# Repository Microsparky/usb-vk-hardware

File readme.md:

# USB Volume Knob

<!--> TODO Readme

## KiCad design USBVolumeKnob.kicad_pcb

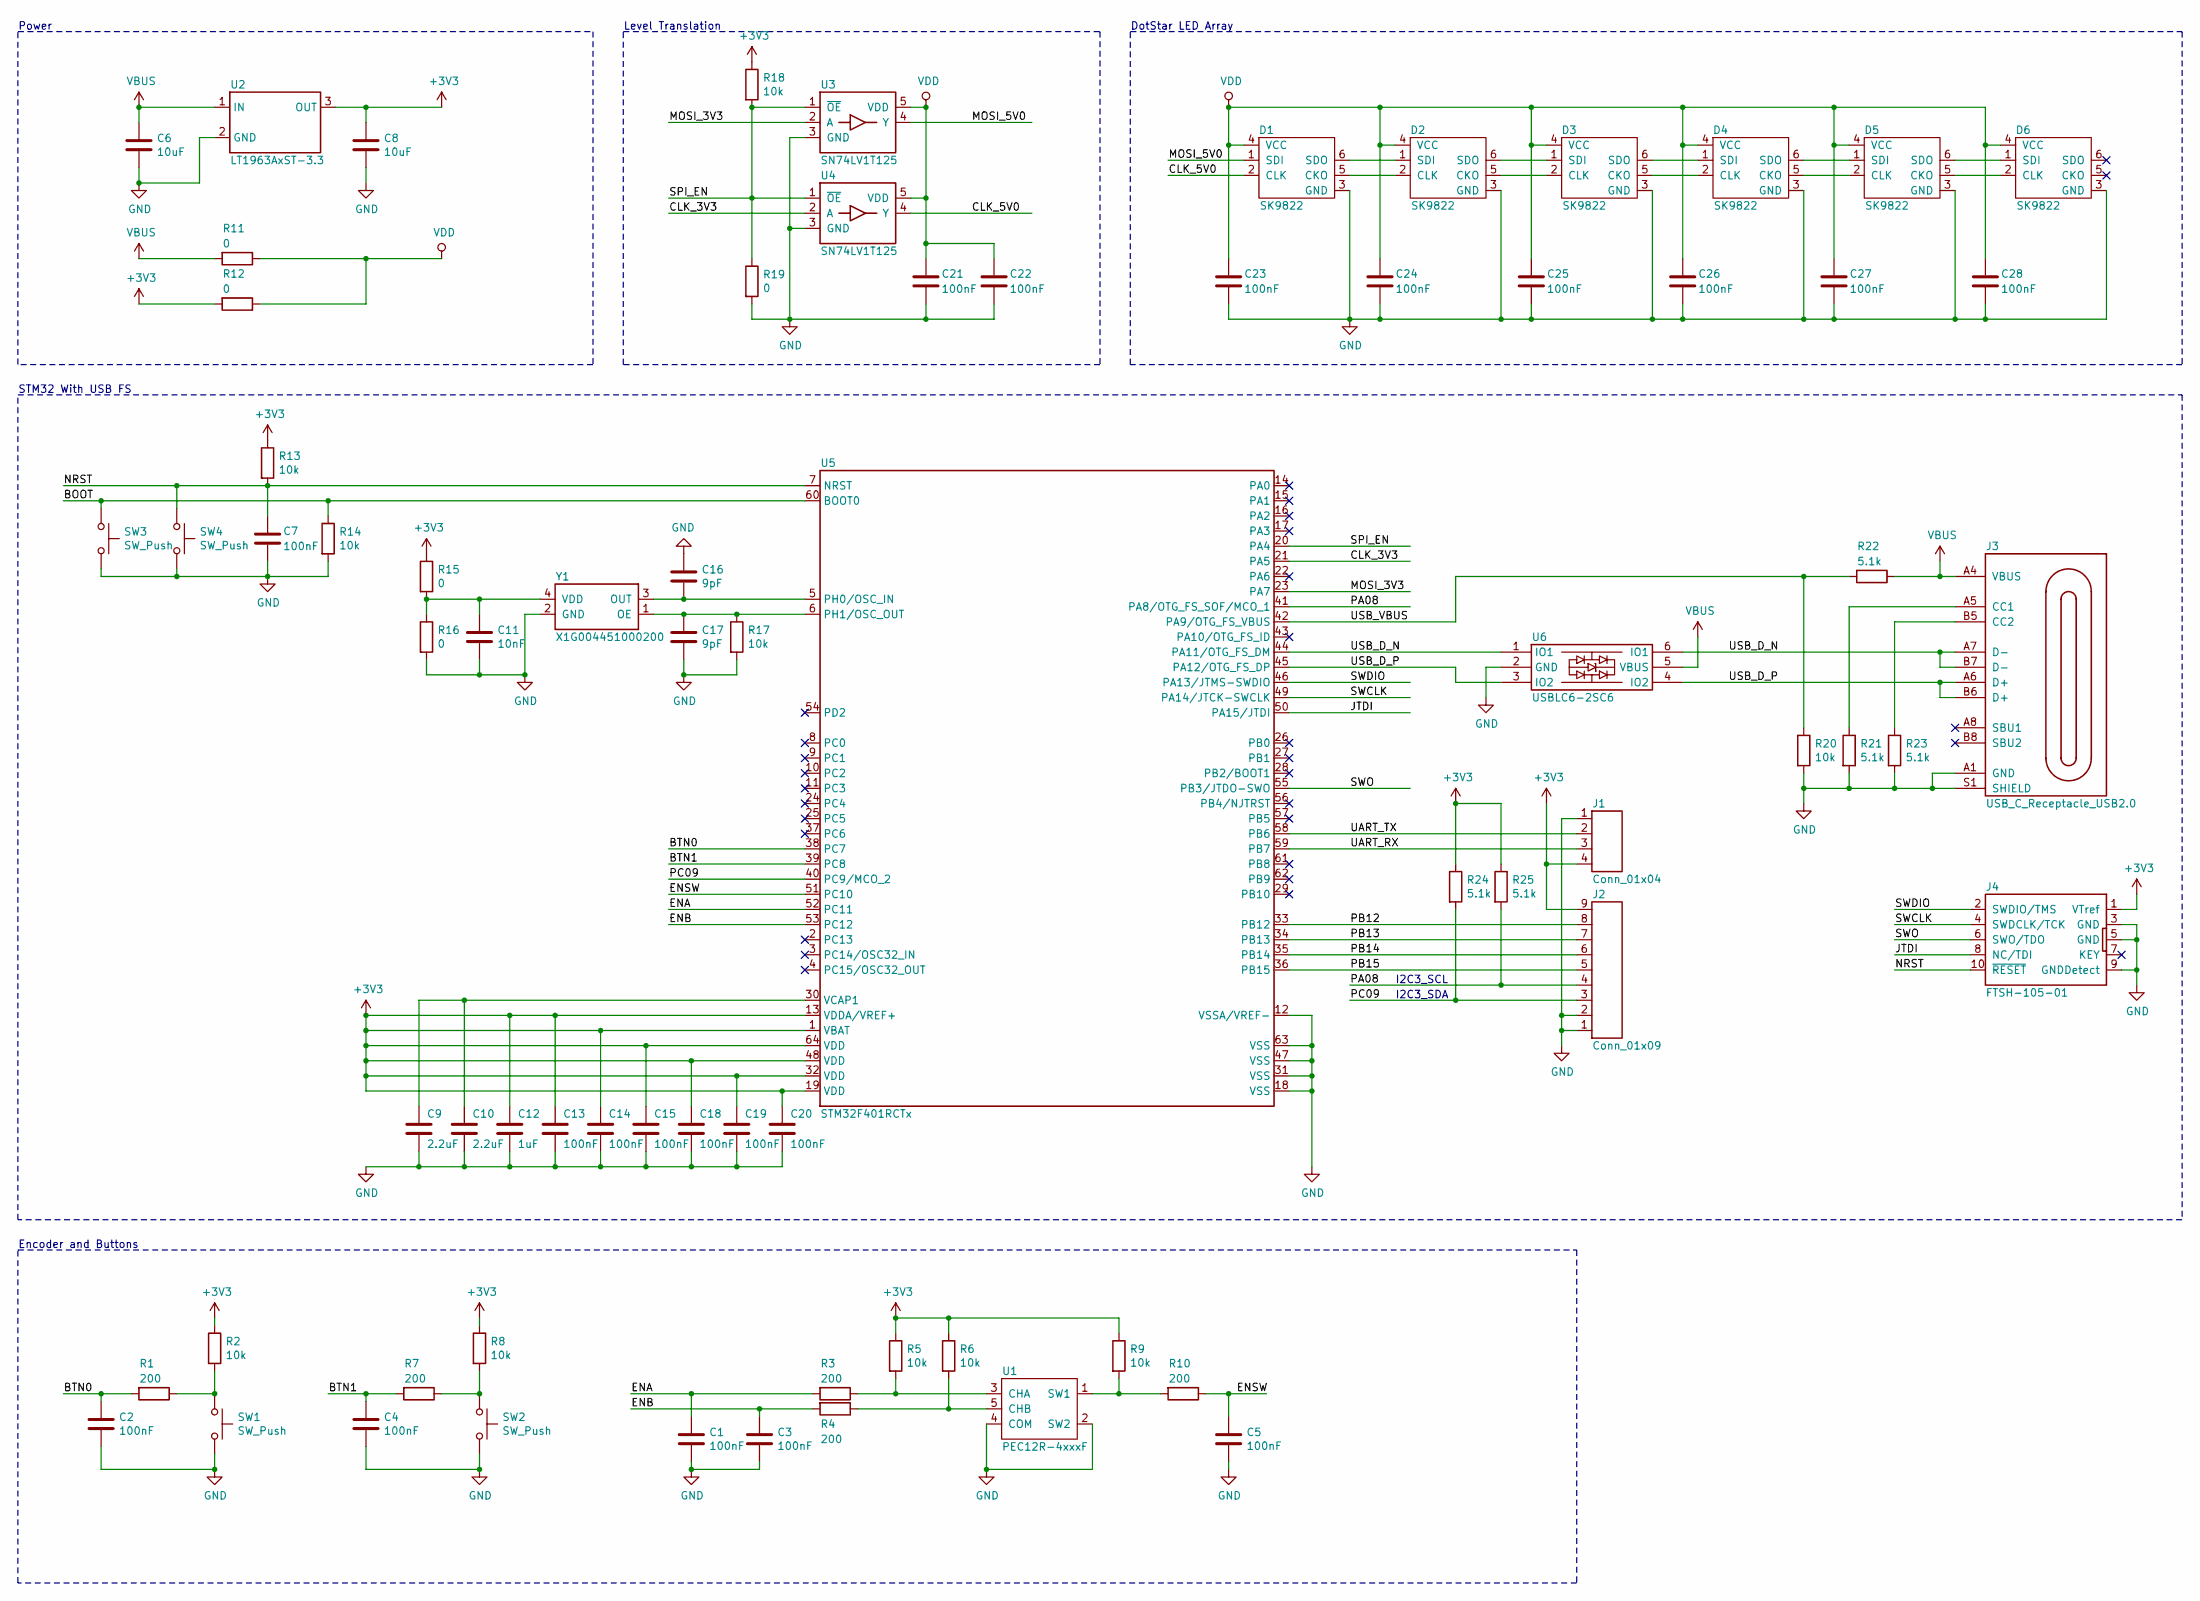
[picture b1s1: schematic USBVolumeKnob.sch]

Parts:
C1, C2, C3, C4, C5, C7, C13, C14, C15, C18, C19, C20, C21, C22, C23, C24, C25, C26, C27, C28: 100nF; C_0603_1608Metric_Pad1.05x0.95mm_HandSolder
C6, C8: 10uF; C_0805_2012Metric_Pad1.15x1.40mm_HandSolder
C9, C10: 2.2uF; C_0805_2012Metric_Pad1.15x1.40mm_HandSolder
C11: 10nF; C_0603_1608Metric_Pad1.05x0.95mm_HandSolder
C12: 1uF; C_0603_1608Metric_Pad1.05x0.95mm_HandSolder
C16, C17: 9pF; C_0402_1005Metric
D1, D2, D3, D4, D5, D6: SK9822; LED_RGB_5050-6
J1: Conn_01x04; Molex_PicoBlade_53261-0471_1x04-1MP_P1.25mm_Horizontal
J2: Conn_01x09; Molex_PicoBlade_53261-0971_1x09-1MP_P1.25mm_Horizontal
J3: USB_C_Receptacle_USB2.0; USB_C_Receptacle_Amphenol_12402012E212A
J4: FTSH-105-01; SAMTEC_FTSH-105-XX-X-DV
R1, R3, R4, R7, R10: 200; R_0603_1608Metric_Pad1.05x0.95mm_HandSolder
R2, R5, R6, R8, R9, R13, R14, R17, R18, R20: 10k; R_0603_1608Metric_Pad1.05x0.95mm_HandSolder
R11, R12, R15, R16, R19: 0; R_0603_1608Metric_Pad1.05x0.95mm_HandSolder
R21, R22, R23, R24, R25: 5.1k; R_0603_1608Metric_Pad1.05x0.95mm_HandSolder
SW1, SW2: SW_Push; B3F-3xxx
SW3, SW4: SW_Push; SW_SPST_B3U-1000P
U1: PEC12R-4xxxF
U2: LT1963AxST-3.3; SOT-223-3_TabPin2
U3, U4: SN74LV1T125; SOT-23-5_HandSoldering
U5: STM32F401RCTx; LQFP-64_10x10mm_P0.5mm
U6: USBLC6-2SC6; SOT-23-6
Y1: X1G004451000200; Crystal_SMD_5032-4Pin_5.0x3.2mm

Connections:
+3V3: C8.1, C12.1, C13.1, C14.1, C15.1, C18.1, C19.1, C20.1, J1.4, J2.9, J4.1 (VTref), R2.1, R5.1, R6.1, R8.1, R9.1, R12.2, R13.1, R15.1, R18.1, R24.1, R25.1, U2.3 (OUT), U5.1 (VBAT), U5.13 (VDDA/VREF+), U5.19 (VDD), U5.32 (VDD), U5.48 (VDD), U5.64 (VDD)
/BOOT: R14.1, SW3.1, U5.60 (BOOT0)
/BTN0: C2.1, R1.2, U5.38 (PC7)
/BTN1: C4.1, R7.2, U5.39 (PC8)
/CLK_3V3: U4.2 (A), U5.21 (PA5)
/CLK_5V0: D1.2 (CLK), U4.4 (Y)
/ENA: C1.1, R3.2, U5.52 (PC11)
/ENB: C3.1, R4.2, U5.53 (PC12)
/ENSW: C5.1, R10.1, U5.51 (PC10)
/JTDI: J4.8 (NC/TDI), U5.50 (PA15/JTDI)
/MOSI_3V3: U3.2 (A), U5.23 (PA7)
/MOSI_5V0: D1.1 (SDI), U3.4 (Y)
/NRST: C7.1, J4.10 (~RESET~), R13.2, SW4.1, U5.7 (NRST)
/PA08: J2.4, R25.2, U5.41 (PA8/OTG_FS_SOF/MCO_1)
/PB12: J2.8, U5.33 (PB12)
/PB13: J2.7, U5.34 (PB13)
/PB14: J2.6, U5.35 (PB14)
/PB15: J2.5, U5.36 (PB15)
/PC09: J2.3, R24.2, U5.40 (PC9/MCO_2)
/SPI_EN: R18.2, R19.1, U3.1 (~OE), U4.1 (~OE), U5.20 (PA4)
/SWCLK: J4.4 (SWDCLK/TCK), U5.49 (PA14/JTCK-SWCLK)
/SWDIO: J4.2 (SWDIO/TMS), U5.46 (PA13/JTMS-SWDIO)
/SWO: J4.6 (SWO/TDO), U5.55 (PB3/JTDO-SWO)
/UART_RX: J1.3, U5.59 (PB7)
/UART_TX: J1.2, U5.58 (PB6)
/USB_D_N: J3.A7 (D-), J3.B7 (D-), U5.44 (PA11/OTG_FS_DM), U6.1 (IO1), U6.6 (IO1)
/USB_D_P: J3.A6 (D+), J3.B6 (D+), U5.45 (PA12/OTG_FS_DP), U6.3 (IO2), U6.4 (IO2)
/USB_VBUS: R20.1, R22.2, U5.42 (PA9/OTG_FS_VBUS)
GND: C1.2, C2.2, C3.2, C4.2, C5.2, C6.2, C7.2, C8.2, C9.2, C10.2, C11.2, C12.2, C13.2, C14.2, C15.2, C16.1, C17.2, C18.2, C19.2, C20.2, C21.2, C22.2, C23.2, C24.2, C25.2, C26.2, C27.2, C28.2, D1.3 (GND), D2.3 (GND), D3.3 (GND), D4.3 (GND), D5.3 (GND), D6.3 (GND), J1.1, J2.1, J2.2, J3.A1 (GND), J3.A12 (GND), J3.B1 (GND), J3.B12 (GND), J3.S1 (SHIELD), J4.3 (GND), J4.5 (GND), J4.9 (GNDDetect), R14.2, R16.2, R17.2, R19.2, R20.2, R21.2, R23.2, SW1.2, SW2.2, SW3.2, SW4.2, U1.2 (SW2), U1.4 (COM), U2.2 (GND), U3.3 (GND), U4.3 (GND), U5.12 (VSSA/VREF-), U5.18 (VSS), U5.31 (VSS), U5.47 (VSS), U5.63 (VSS), U6.2 (GND), Y1.2 (GND)
unnamed: C9.1, C10.1, U5.30 (VCAP1)
unnamed: C11.1, R15.2, R16.1, Y1.4 (VDD)
unnamed: C16.2, U5.5 (PH0/OSC_IN), Y1.3 (OUT)
unnamed: C17.1, R17.1, U5.6 (PH1/OSC_OUT), Y1.1 (OE)
unnamed: D1.5 (CKO), D2.2 (CLK)
unnamed: D1.6 (SDO), D2.1 (SDI)
unnamed: D2.5 (CKO), D3.2 (CLK)
unnamed: D2.6 (SDO), D3.1 (SDI)
unnamed: D3.5 (CKO), D4.2 (CLK)
unnamed: D3.6 (SDO), D4.1 (SDI)
unnamed: D4.5 (CKO), D5.2 (CLK)
unnamed: D4.6 (SDO), D5.1 (SDI)
unnamed: D5.5 (CKO), D6.2 (CLK)
unnamed: D5.6 (SDO), D6.1 (SDI)
unnamed: J3.A5 (CC1), R21.1
unnamed: J3.B5 (CC2), R23.1
unnamed: R1.1, R2.2, SW1.1
unnamed: R3.1, R5.2, U1.3 (CHA)
unnamed: R4.1, R6.2, U1.5 (CHB)
unnamed: R7.1, R8.2, SW2.1
unnamed: R9.2, R10.2, U1.1 (SW1)
VBUS: C6.1, J3.A4 (VBUS), J3.A9 (VBUS), J3.B4 (VBUS), J3.B9 (VBUS), R11.2, R22.1, U2.1 (IN), U6.5 (VBUS)
VDD: C21.1, C22.1, C23.1, C24.1, C25.1, C26.1, C27.1, C28.1, D1.4 (VCC), D2.4 (VCC), D3.4 (VCC), D4.4 (VCC), D5.4 (VCC), D6.4 (VCC), R11.1, R12.1, U3.5 (VDD), U4.5 (VDD)

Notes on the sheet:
Power
Level Translation
DotStar LED Array
STM32 With USB FS
Encoder and Buttons
I2C3_SDA
I2C3_SCL

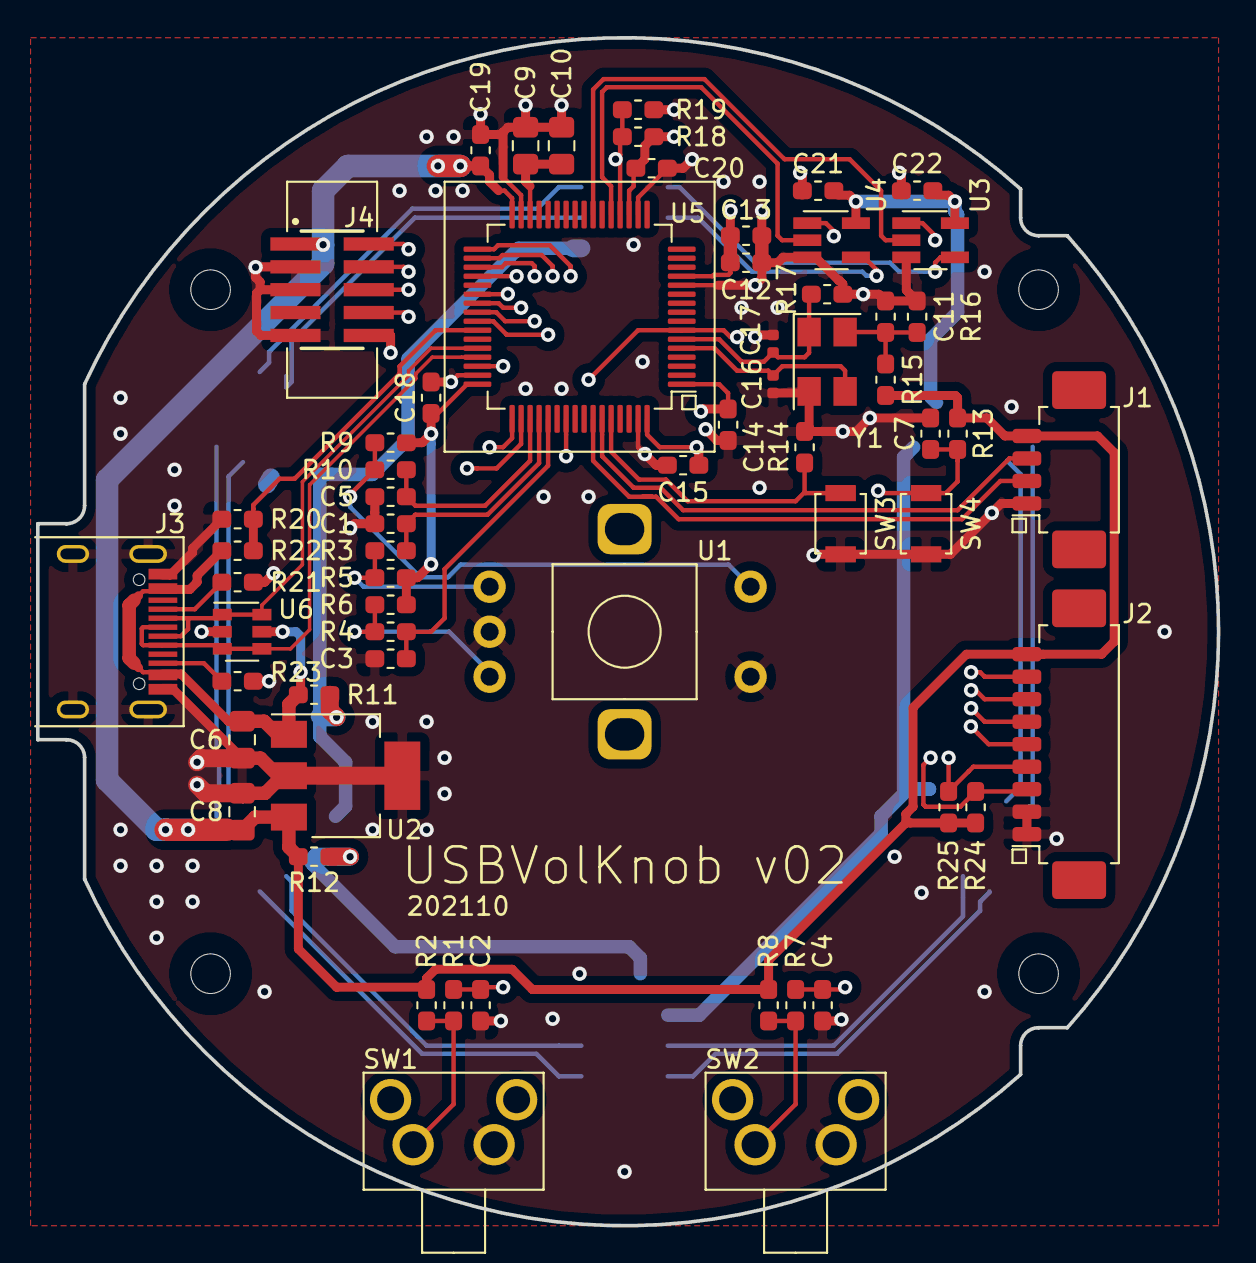
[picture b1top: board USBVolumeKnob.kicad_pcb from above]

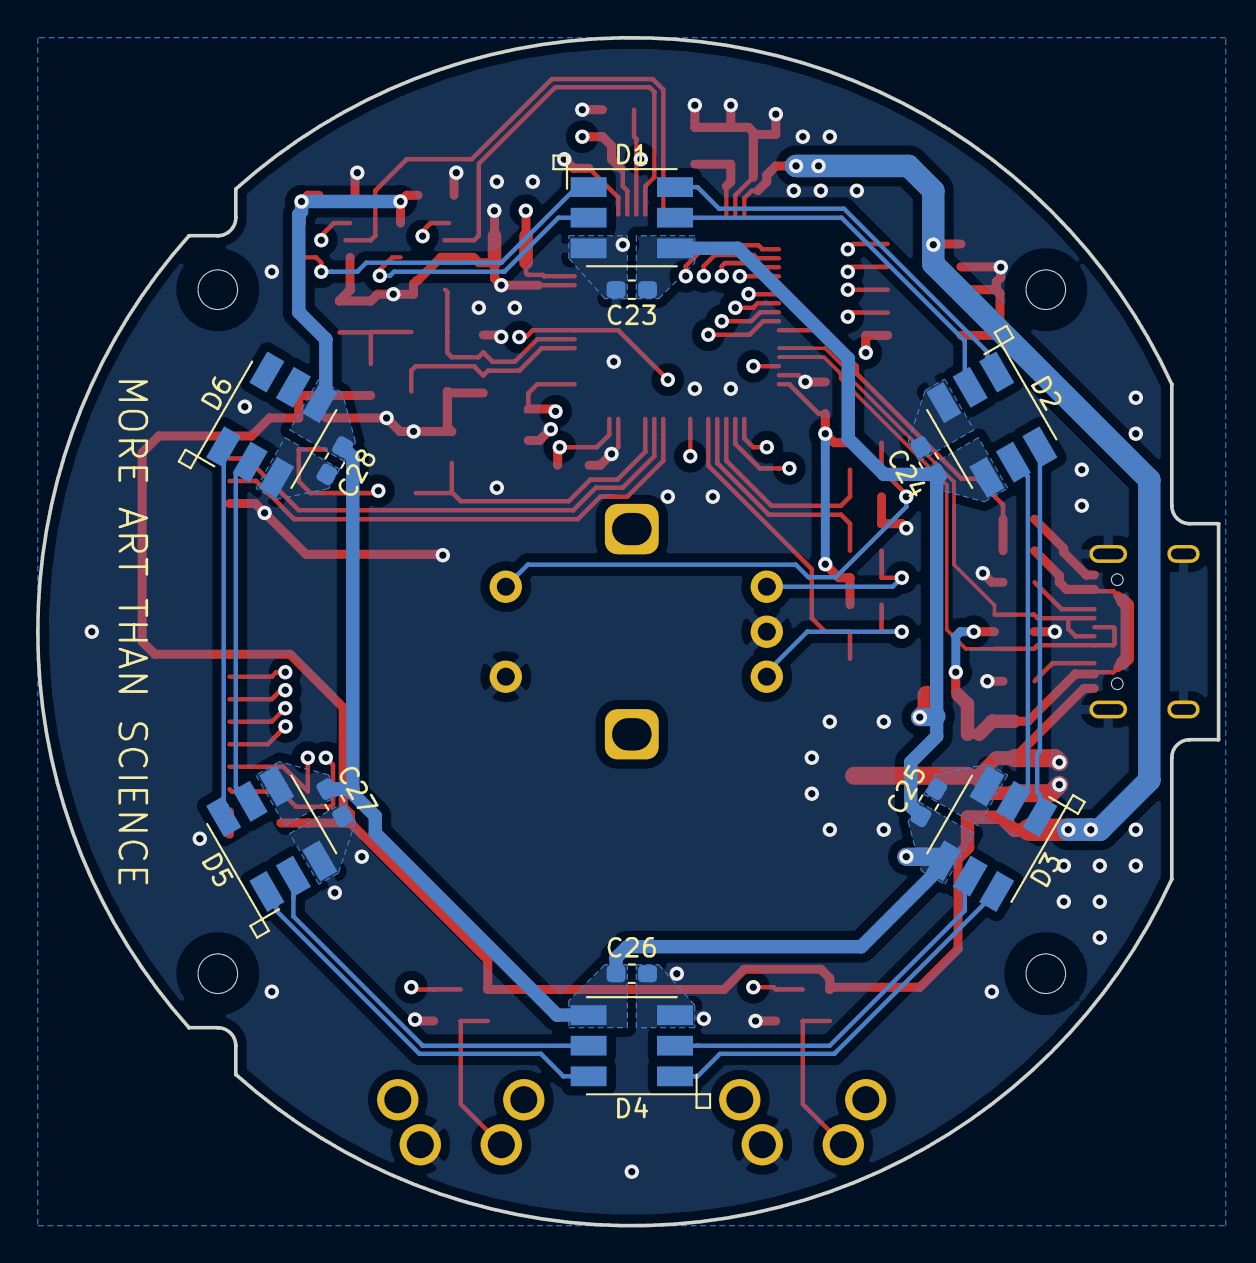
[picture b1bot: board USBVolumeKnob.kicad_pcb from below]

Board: 4 copper layers, 65.6 x 66.0 mm, 78 parts (12 on the bottom side), 52 nets.

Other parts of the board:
M1, M2, M3, M4: MountingHole_2.2mm_M2_ISO14580

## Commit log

2021-06-29 Initial commit of v1
2021-08-10 Added custom library components and 3D data
2021-10-14 Schamatic complete, component placement complete
2021-10-28 Completed v02. Final schematic and layout.
2021-11-15 Create LICENSE
